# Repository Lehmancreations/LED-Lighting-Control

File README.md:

This project is for the LehmanCreations LED Lighting controller

See the website http://lehmancreations.com/ledcontroller for more info

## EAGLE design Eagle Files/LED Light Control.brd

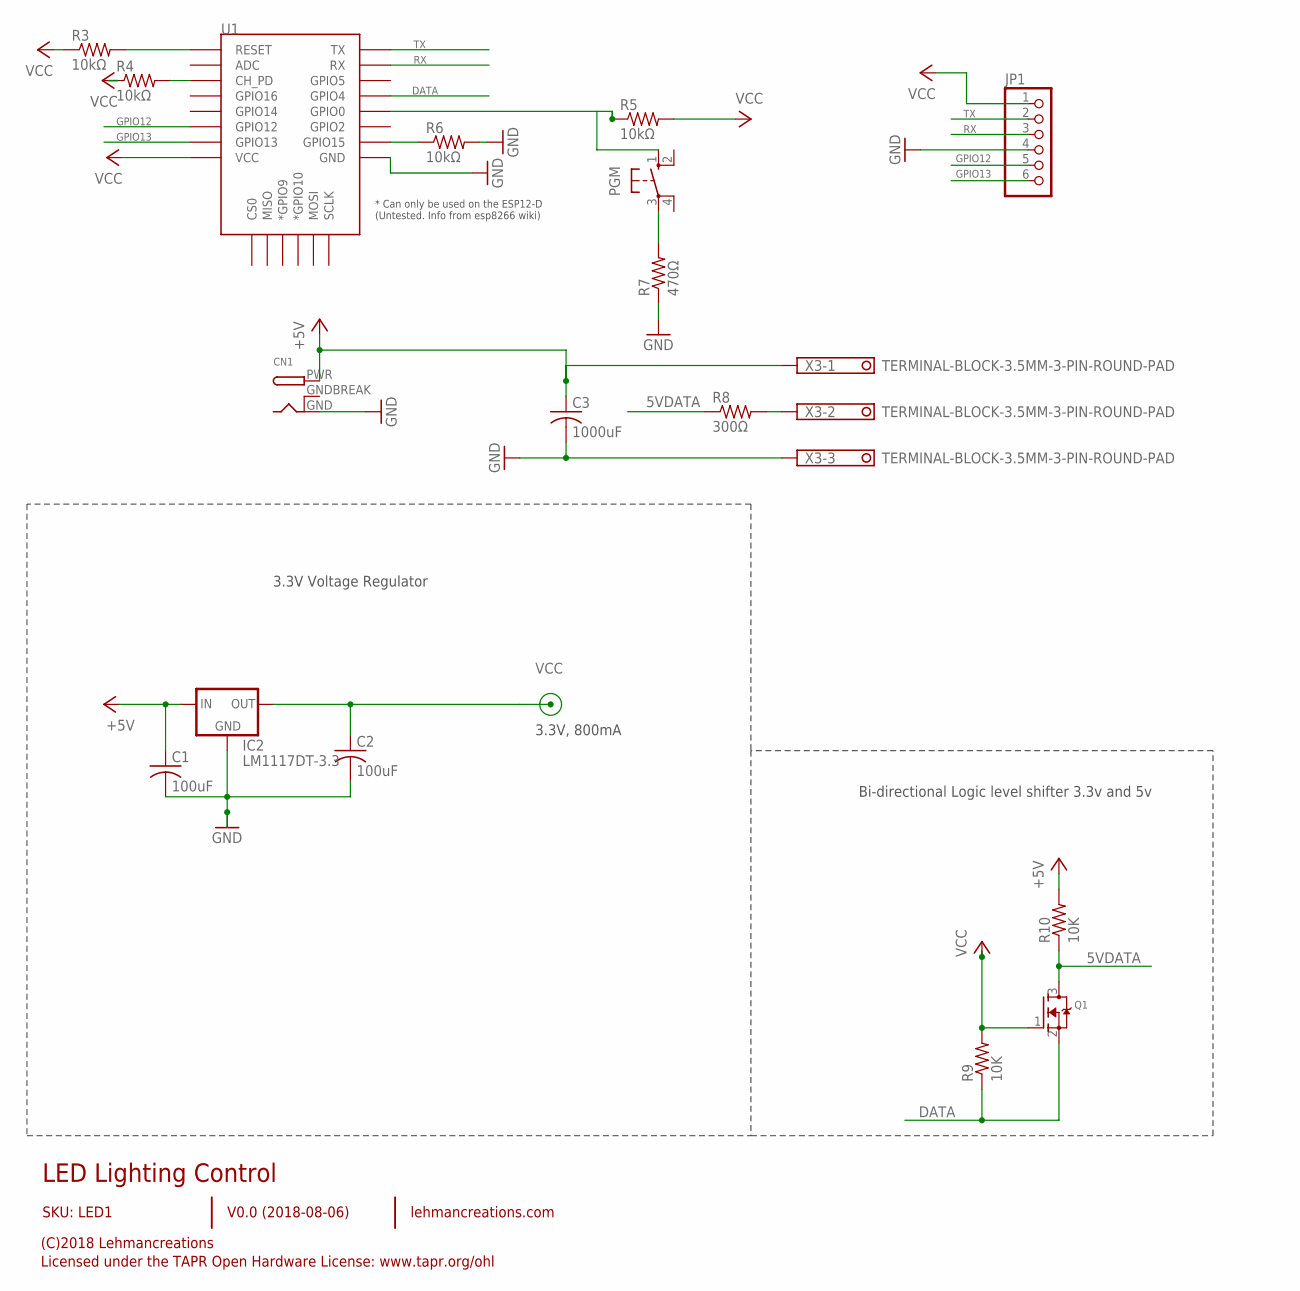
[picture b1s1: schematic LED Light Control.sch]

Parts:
C1, C2: 100uF; C0805
C3: 1000uF; C0805
CN1: DCBARRELPTH; DCJACK_2MM_PTH
IC2: LM1117DT-3.3; TO252
JP1: PINHD-1X6; 1X06
PGM: 10-XX; B3F-10XX
Q1: MOSFET-NWAVE; SOT23-W
R3, R4, R5, R6: 10kΩ; R0805
R7: 470Ω; R0805
R8: 300Ω; R0805
R9, R10: 10K; R0805
U1: ESP12ESMD; ESP12E-SMD
X3: TERMINAL-BLOCK-3.5MM-3-PIN-ROUND-PAD; TERMINAL-BLOCK-3-PIN-3.5MM-ROUND-PAD

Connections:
5VDATA: Q1.3 (D), R8.1, R10.1
+5V: C1.1, C3.1, CN1.PWR, IC2.2 (IN), R10.2, X3.1
DATA: Q1.2 (S), R9.1, U1.GPIO4
GND: C1.2, C2.2, C3.2, CN1.GND, IC2.1 (GND), JP1.4, R6.2, R7.1, U1.GND, X3.3
GNDBREAK: CN1.GNDBREAK
GPIO0: PGM.1 (S), R5.1, U1.GPIO0
GPIO12: JP1.5, U1.GPIO12
GPIO13: JP1.6, U1.GPIO13
unnamed: R3.2, U1.RESET
unnamed: R4.2, U1.CH_PD
unnamed: R6.1, U1.GPIO15
unnamed: PGM.3, R7.2
unnamed: R8.2, X3.2
RX: JP1.3, U1.RXD0 (RX)
TX: JP1.2, U1.TXD0 (TX)
VCC: C2.1, IC2.3 (OUT), JP1.1, Q1.1 (G), R3.1, R4.1, R5.2, R9.2, U1.VCC

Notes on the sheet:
3.3V Voltage Regulator
3.3V, 800mA
LED Lighting Control
V0.0 (2018-08-06)
SKU: LED1
(C)2018 Lehmancreations
Licensed under the TAPR Open Hardware License: www.tapr.org/ohl
lehmancreations.com
Bi-directional Logic level shifter 3.3v and 5v

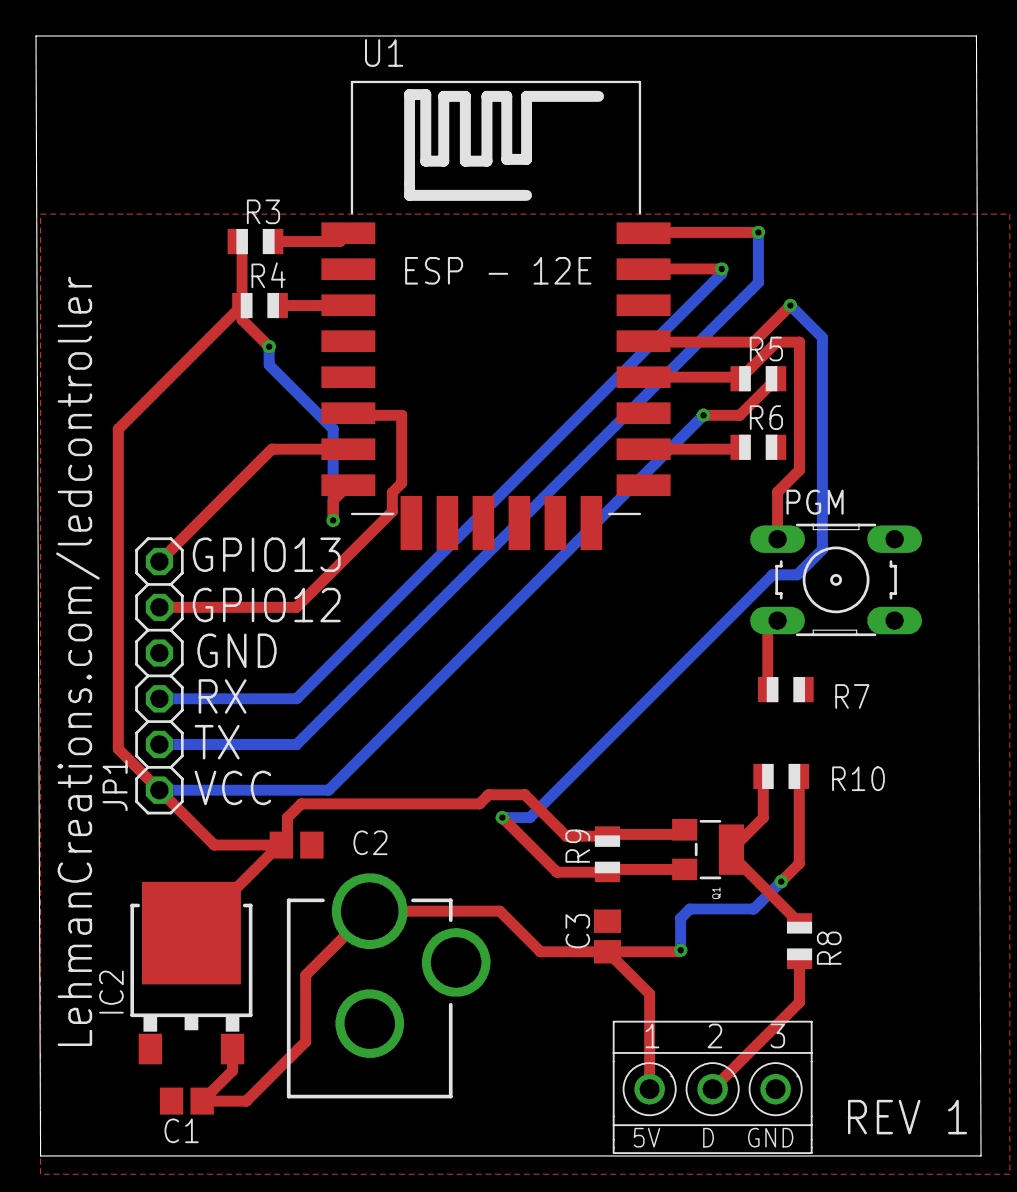
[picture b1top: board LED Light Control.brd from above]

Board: 2 copper layers, 52.5 x 62.2 mm, 18 parts (0 on the bottom side), 15 nets.

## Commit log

2018-08-15 Added plans for the board
2018-10-17 Complete redisign of board. Also changed out the regulator on the schematic for a new one
2018-11-03 Made board smaller and added lables
2018-11-03 Made board smaller
2018-11-03 Clean up Schematic
2018-11-05 Changed the ground plane to be lower than the antenna
2018-11-07 Added LehmanCreations to the back of the board
2018-11-07 Moved the logo a bit
2018-11-07 no message
2018-11-07 Moved logo to bNames layer
2018-11-07 Fix logo
2018-11-13 Uploaded a render of the board
2018-11-13 Added render of board
2018-11-13 Moved render
2019-12-16 Tied Ground pin on ESP12E to the GND
2019-12-18 Changed the size of the board to be smaller

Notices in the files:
parts and their libraries:
lm1117: (c) 2014 Samuel Lourenço
